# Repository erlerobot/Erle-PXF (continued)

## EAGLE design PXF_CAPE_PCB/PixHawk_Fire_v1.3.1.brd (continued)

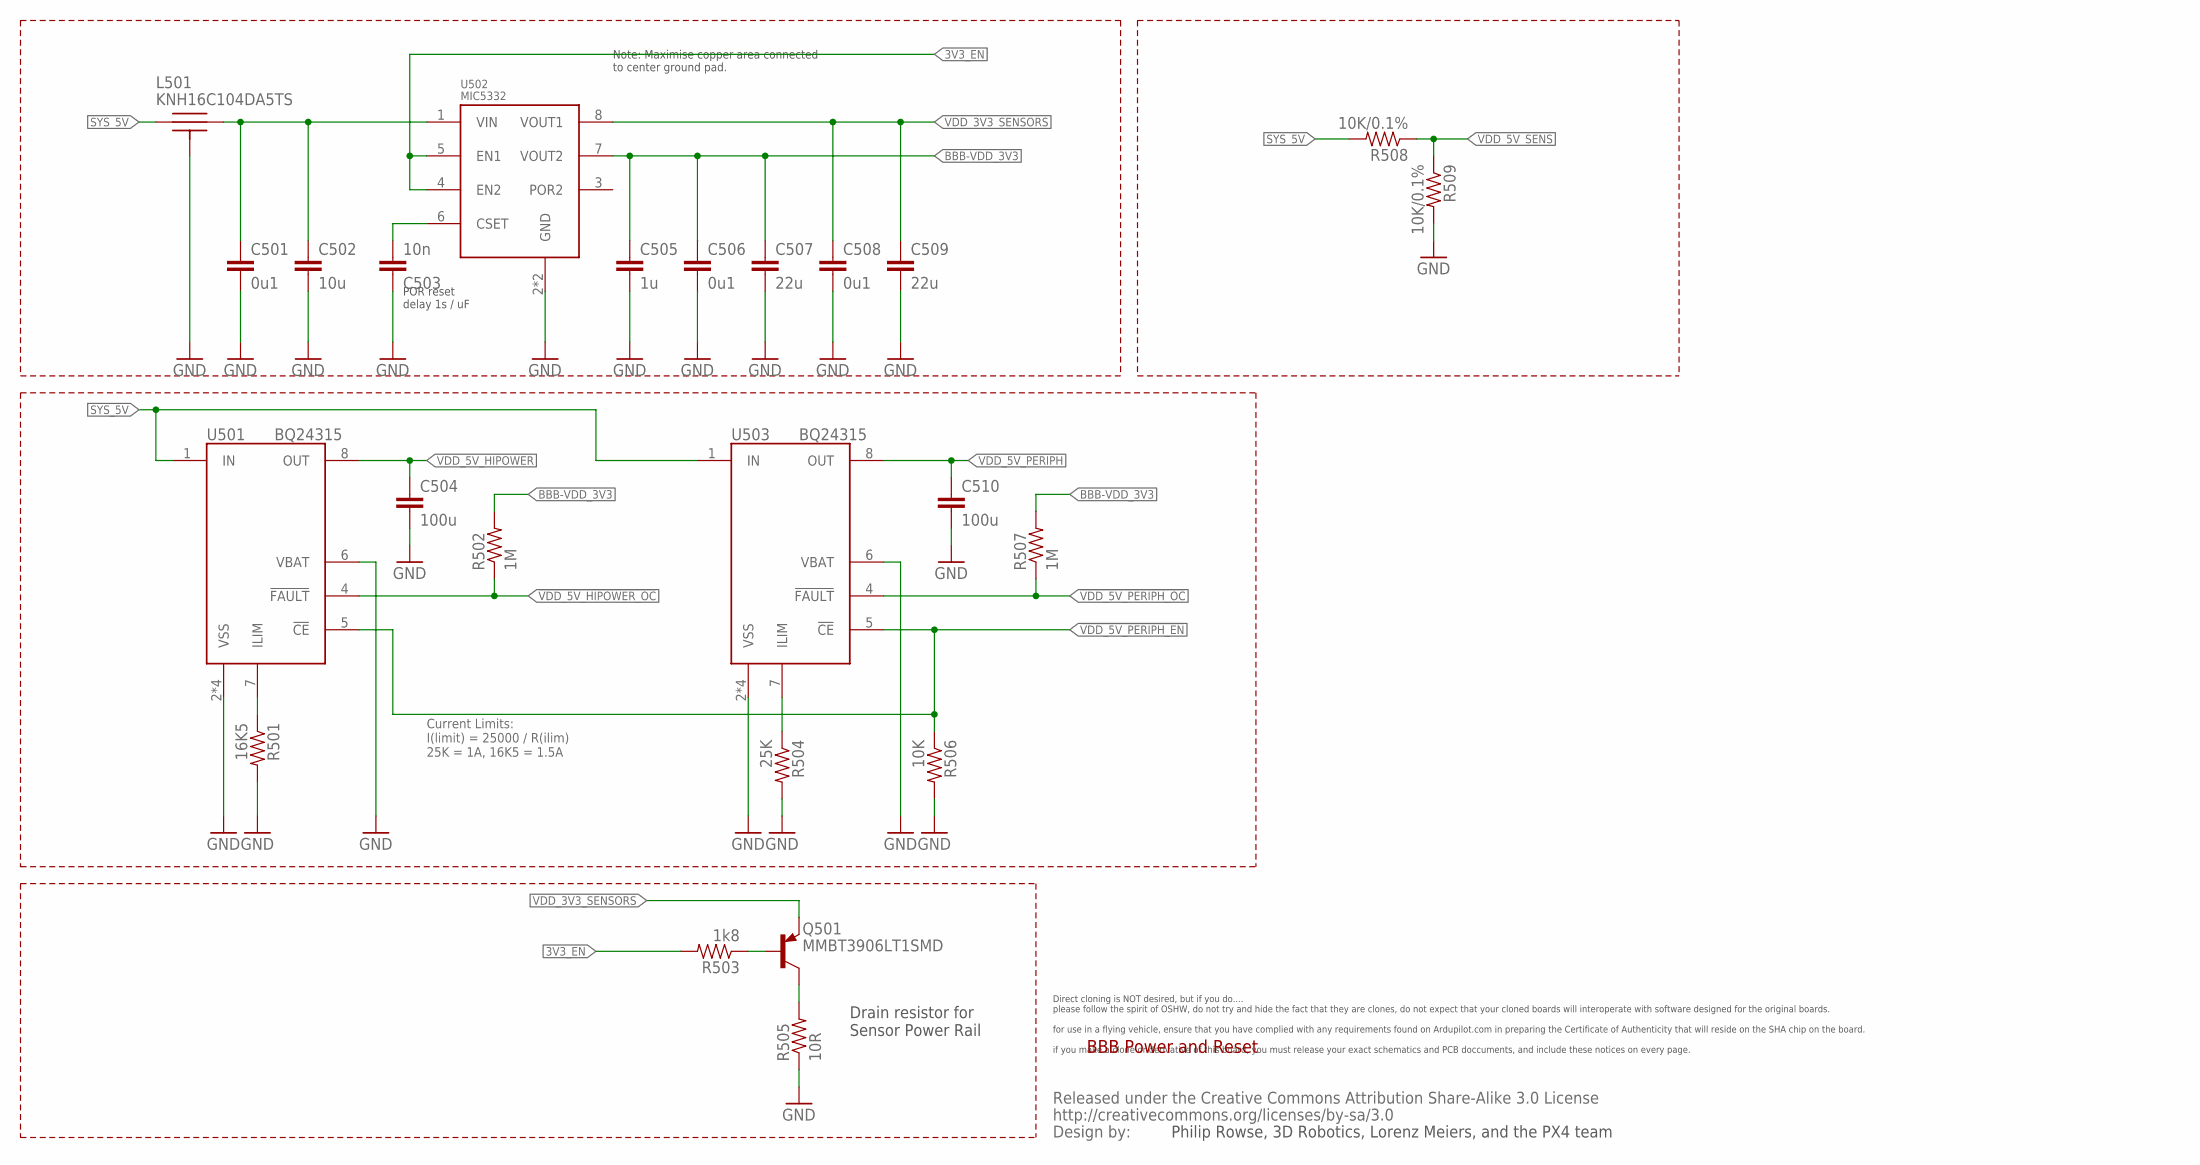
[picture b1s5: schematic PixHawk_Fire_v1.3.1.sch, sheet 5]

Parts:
C501, C506, C508: 0u1; 0402-CAP; PARTNO CC0402ZRY5V7BB104
C502: 10u; 0805-CAP; PARTNO C1608X7S0J106M080AC
C503: 10n; 0402-CAP; PARTNO CC0402KRX7R7BB103
C504, C510: 100u; 1206-CAP; PARTNO C3216X5R1A107M160AC
C505: 1u; 0603-CAP; PARTNO CC0603ZRY5V7BB105
C507, C509: 22u; 0805-CAP; PARTNO CC0805MKX5R5BB226
L501: KNH16C104DA5TS; KYOCERA-KNH16-DA; PARTNO KNH16C104DA5TS
Q501: MMBT3906LT1SMD; SOT23-BEC; PARTNO MMBT3906LT1G
R501: 16K5; 0402-RES; PARTNO RMCF0402FT16K5
R502, R507: 1M; 0402-RES; PARTNO MCR01MRTF1004
R503: 1k8; 0402-RES; PARTNO RC0402FR-071K8L
R504: 25K; 0402-RES; PARTNO RMCF0402FT25K5
R505: 10R; 0603-RES; PARTNO RC0402FR-0710RL
R506: 10K; 0402-RES; PARTNO ERA-2AEB103X
R508, R509: 10K/0.1%; 0402-RES; PARTNO ERA-2AEB103X
U501, U503: BQ24315; QFN8-DSG; PARTNO BQ24315DSGR
U502: MIC5332; MLF-8-EPAD; PARTNO MIC5332-SSYMT
U$9: CREATIVE_COMMONS

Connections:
3V3_EN: R503.P$2 (2), U502.4 (EN2), U502.5 (EN1); also elsewhere on the board
!VDD_5V_HIPOWER_OC: R502.P$1 (1), U501.4 (!FAULT); also elsewhere on the board
!VDD_5V_PERIPH_EN: R506.P$1 (1), U501.5 (!CE), U503.5 (!CE); also elsewhere on the board
!VDD_5V_PERIPH_OC: R507.P$1 (1), U503.4 (!FAULT); also elsewhere on the board
BBB-VDD_3V3: C505.P$1 (1), C506.P$1 (1), C507.P$1 (1), R502.P$2 (2), R507.P$2 (2), U502.7 (VOUT2); also elsewhere on the board
FMU-VDD_5V5: C501.P$1 (1), C502.P$1 (1), L501.P$2, U502.1 (VIN)
GND: C501.P$2 (2), C502.P$2 (2), C503.P$1 (1), C504.P$2 (2), C505.P$2 (2), C506.P$2 (2), C507.P$2 (2), C508.P$2 (2), C509.P$2 (2), C510.P$2 (2), L501.P$3, L501.P$4, L501.P$5, R501.P$2 (2), R504.P$2 (2), R505.1, R506.P$2 (2), R509.P$2 (2), U501.2 (VSS), U501.6 (VBAT), U501.GND (VSS), U501.P$2 (VSS), U501.P$3 (VSS), U502.2 (GND), U502.GND, U503.2 (VSS), U503.6 (VBAT), U503.GND (VSS), U503.P$2 (VSS), U503.P$3 (VSS); also elsewhere on the board
unnamed: C503.P$2 (2), U502.6 (CSET)
unnamed: R504.P$1 (1), U503.7 (ILIM)
unnamed: Q501.C, R505.2
unnamed: Q501.B, R503.P$1 (1)
unnamed: R501.P$1 (1), U501.7 (ILIM)
SYS_5V: L501.P$1, R508.P$2 (2), U501.1 (IN), U503.1 (IN); also elsewhere on the board
VDD_3V3_SENSORS: C508.P$1 (1), C509.P$1 (1), Q501.E, U502.8 (VOUT1); also elsewhere on the board
VDD_5V_HIPOWER: C504.P$1 (1), U501.8 (OUT); also elsewhere on the board
VDD_5V_PERIPH: C510.P$1 (1), U503.8 (OUT); also elsewhere on the board
VDD_5V_SENS: R508.P$1 (1), R509.P$1 (1); also elsewhere on the board

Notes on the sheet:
BBB Power and Reset
Note: Maximise copper area connected to center ground pad.
POR reset delay 1s / uF
Current Limits: I(limit) = 25000 / R(ilim) 25K = 1A, 16K5 = 1.5A
Drain resistor for Sensor Power Rail
Philip Rowse, 3D Robotics, Lorenz Meiers, and the PX4 team
Direct cloning is NOT desired, but if you do.... please follow the spirit of OSHW, do not try and hide the fact that they are clones, do not expect that your cloned boards will interoperate with software designed for the original boards. for use in a flying vehicle, ensure that you have complied wi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

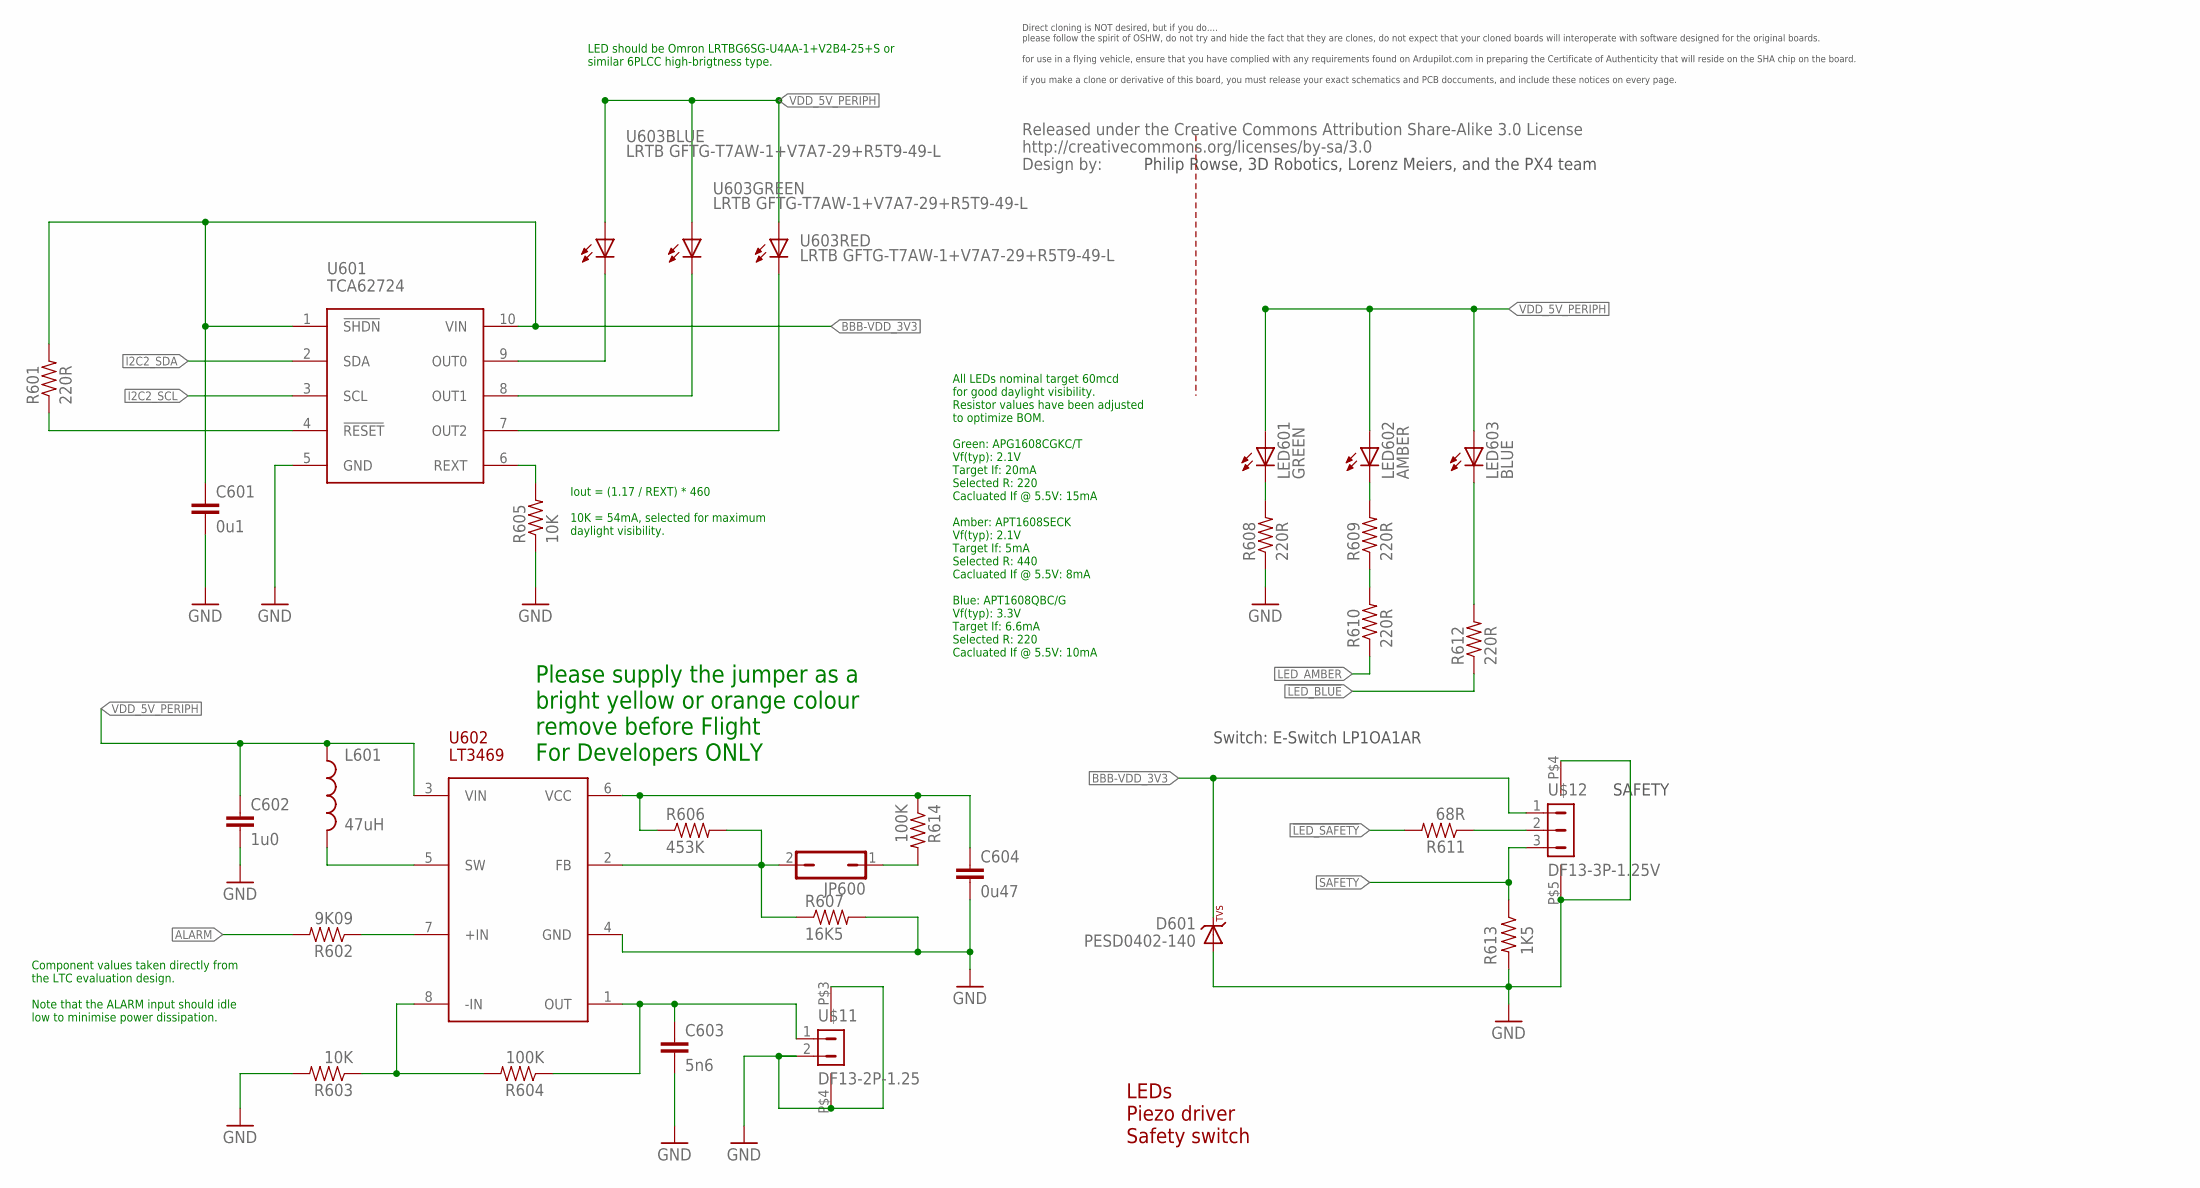
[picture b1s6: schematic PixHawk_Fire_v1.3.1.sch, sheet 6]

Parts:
C601: 0u1; 0402-CAP; PARTNO CC0402ZRY5V7BB104
C602: 1u0; 0603-CAP; PARTNO CC0603ZRY5V7BB105
C603: 5n6; 0402-CAP; PARTNO CC0402KRX7R7BB562
C604: 0u47; 0402-CAP; PARTNO C1005X5R1C474K050BC
D601: PESD0402-140; 0402-TVS; PARTNO PESD0402-140
JP600: JP1Q; JP1; PARTNO 1-87215-0
L601: 47uH; 0805-IND; PARTNO MLZ2012M470W
LED601: GREEN; 0603-LED; PARTNO APTD1608CGCK
LED602: AMBER; 0603-LED; PARTNO APTD1608SECK
LED603: BLUE; 0603-LED; PARTNO APTD1608QBC/D
R601, R608, R609, R610, R612: 220R; 0402-RES; PARTNO RC0402FR-07220RL
R602: 9K09; 0402-RES; PARTNO RMCF0402FT9K09
R603, R605: 10K; 0402-RES; PARTNO ERA-2AEB103X
R604, R614: 100K; 0402-RES; PARTNO RC0402FR-07100KL
R606: 453K; 0402-RES; PARTNO RMCF0402FT453K
R607: 16K5; 0402-RES; PARTNO RMCF0402FT16K5
R611: 68R; 0402-RES; PARTNO RC0402FR-0768RL
R613: 1K5; 0402-RES; PARTNO RC0402FR-071K5L
U601: TCA62724FMG; SON10; PARTNO TCA62724FMG
U602: LT3469; SOT23-8; PARTNO LT3469ETS8
U603: LRTB GFTG-T7AW-1+V7A7-29+R5T9-49-L; 6-PLCC; PARTNO LRTB GFTG-T7AW-1+V7A7-29+R5T9-49-L
U$10: CREATIVE_COMMONS
U$11: DF13-2P-1.25; DF13C-2P-1.25V; PARTNO DF13C-2P-1.25V(20)
U$12: DF13-3P-1.25V; DF13C-3P-1.25V; PARTNO DF13C-3P-1.25V(20)

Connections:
!LED_AMBER: R610.P$1 (1); also elsewhere on the board
!LED_BLUE: R612.P$1 (1); also elsewhere on the board
!LED_SAFETY: R611.P$2 (2); also elsewhere on the board
ALARM: R602.P$2 (2); also elsewhere on the board
BBB-VDD_3V3: C601.P$1 (1), D601.C, R601.P$2 (2), U601.1 (!SHDN), U601.10 (VIN), U$12.1; also elsewhere on the board
GND: C601.P$2 (2), C602.P$2 (2), C603.P$2 (2), C604.P$2 (2), D601.A, R603.P$2 (2), R605.P$1 (1), R607.P$2 (2), R608.P$1 (1), R613.P$2 (2), U601.5 (GND), U602.4 (GND), U$11.2, U$11.P$3, U$11.P$4, U$12.P$4, U$12.P$5; also elsewhere on the board
I2C2_SCL: U601.3 (SCL); also elsewhere on the board
I2C2_SDA: U601.2 (SDA); also elsewhere on the board
unnamed: R601.P$1 (1), U601.4 (!RESET)
unnamed: LED603.C, R612.P$2 (2)
unnamed: JP600.2, R606.P$2 (2), R607.P$1 (1), U602.2 (FB)
unnamed: R603.P$1 (1), R604.P$2 (2), U602.8 (-IN)
unnamed: C603.P$1 (1), R604.P$1 (1), U602.1 (OUT), U$11.1
unnamed: R602.P$1 (1), U602.7 (+IN)
unnamed: LED601.C, R608.P$2 (2)
unnamed: L601.P$2 (2), U602.5 (SW)
unnamed: C604.P$1 (1), R606.P$1 (1), R614.P$1 (1), U602.6 (VCC)
unnamed: R609.P$1 (1), R610.P$2 (2)
unnamed: LED602.C, R609.P$2 (2)
unnamed: JP600.1, R614.P$2 (2)
unnamed: R611.P$1 (1), U$12.2
unnamed: R605.P$2 (2), U601.6 (REXT)
RGB_LED_3: U601.9 (OUT0), U603.C1 (C)
RGB_LED_4: U601.8 (OUT1), U603.C2 (C)
RGB_LED_14: U601.7 (OUT2), U603.C3 (C)
SAFETY: R613.P$1 (1), U$12.3; also elsewhere on the board
VDD_5V_PERIPH: C602.P$1 (1), L601.P$1 (1), LED601.A, LED602.A, LED603.A, U602.3 (VIN), U603.A1 (A), U603.A2 (A), U603.A3 (A); also elsewhere on the board

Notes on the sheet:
LEDs Piezo driver Safety switch
Switch: E-Switch LP1OA1AR
SAFETY
LED should be Omron LRTBG6SG-U4AA-1+V2B4-25+S or similar 6PLCC high-brigtness type.
Iout = (1.17 / REXT) * 460 10K = 54mA, selected for maximum daylight visibility.
All LEDs nominal target 60mcd for good daylight visibility. Resistor values have been adjusted to optimize BOM. Green: APG1608CGKC/T Vf(typ): 2.1V Target If: 20mA Selected R: 220 Cacluated If @ 5.5V: 15mA Amber: APT1608SECK Vf(typ): 2.1V Target If: 5mA Selected R: 440 Cacluated If @ 5.5V: 8mA Blue: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
Component values taken directly from the LTC evaluation design. Note that the ALARM input should idle low to minimise power dissipation.
Please supply the jumper as a bright yellow or orange colour remove before Flight For Developers ONLY
Philip Rowse, 3D Robotics, Lorenz Meiers, and the PX4 team
Direct cloning is NOT desired, but if you do.... please follow the spirit of OSHW, do not try and hide the fact that they are clones, do not expect that your cloned boards will interoperate with software designed for the original boards. for use in a flying vehicle, ensure that you have complied wi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

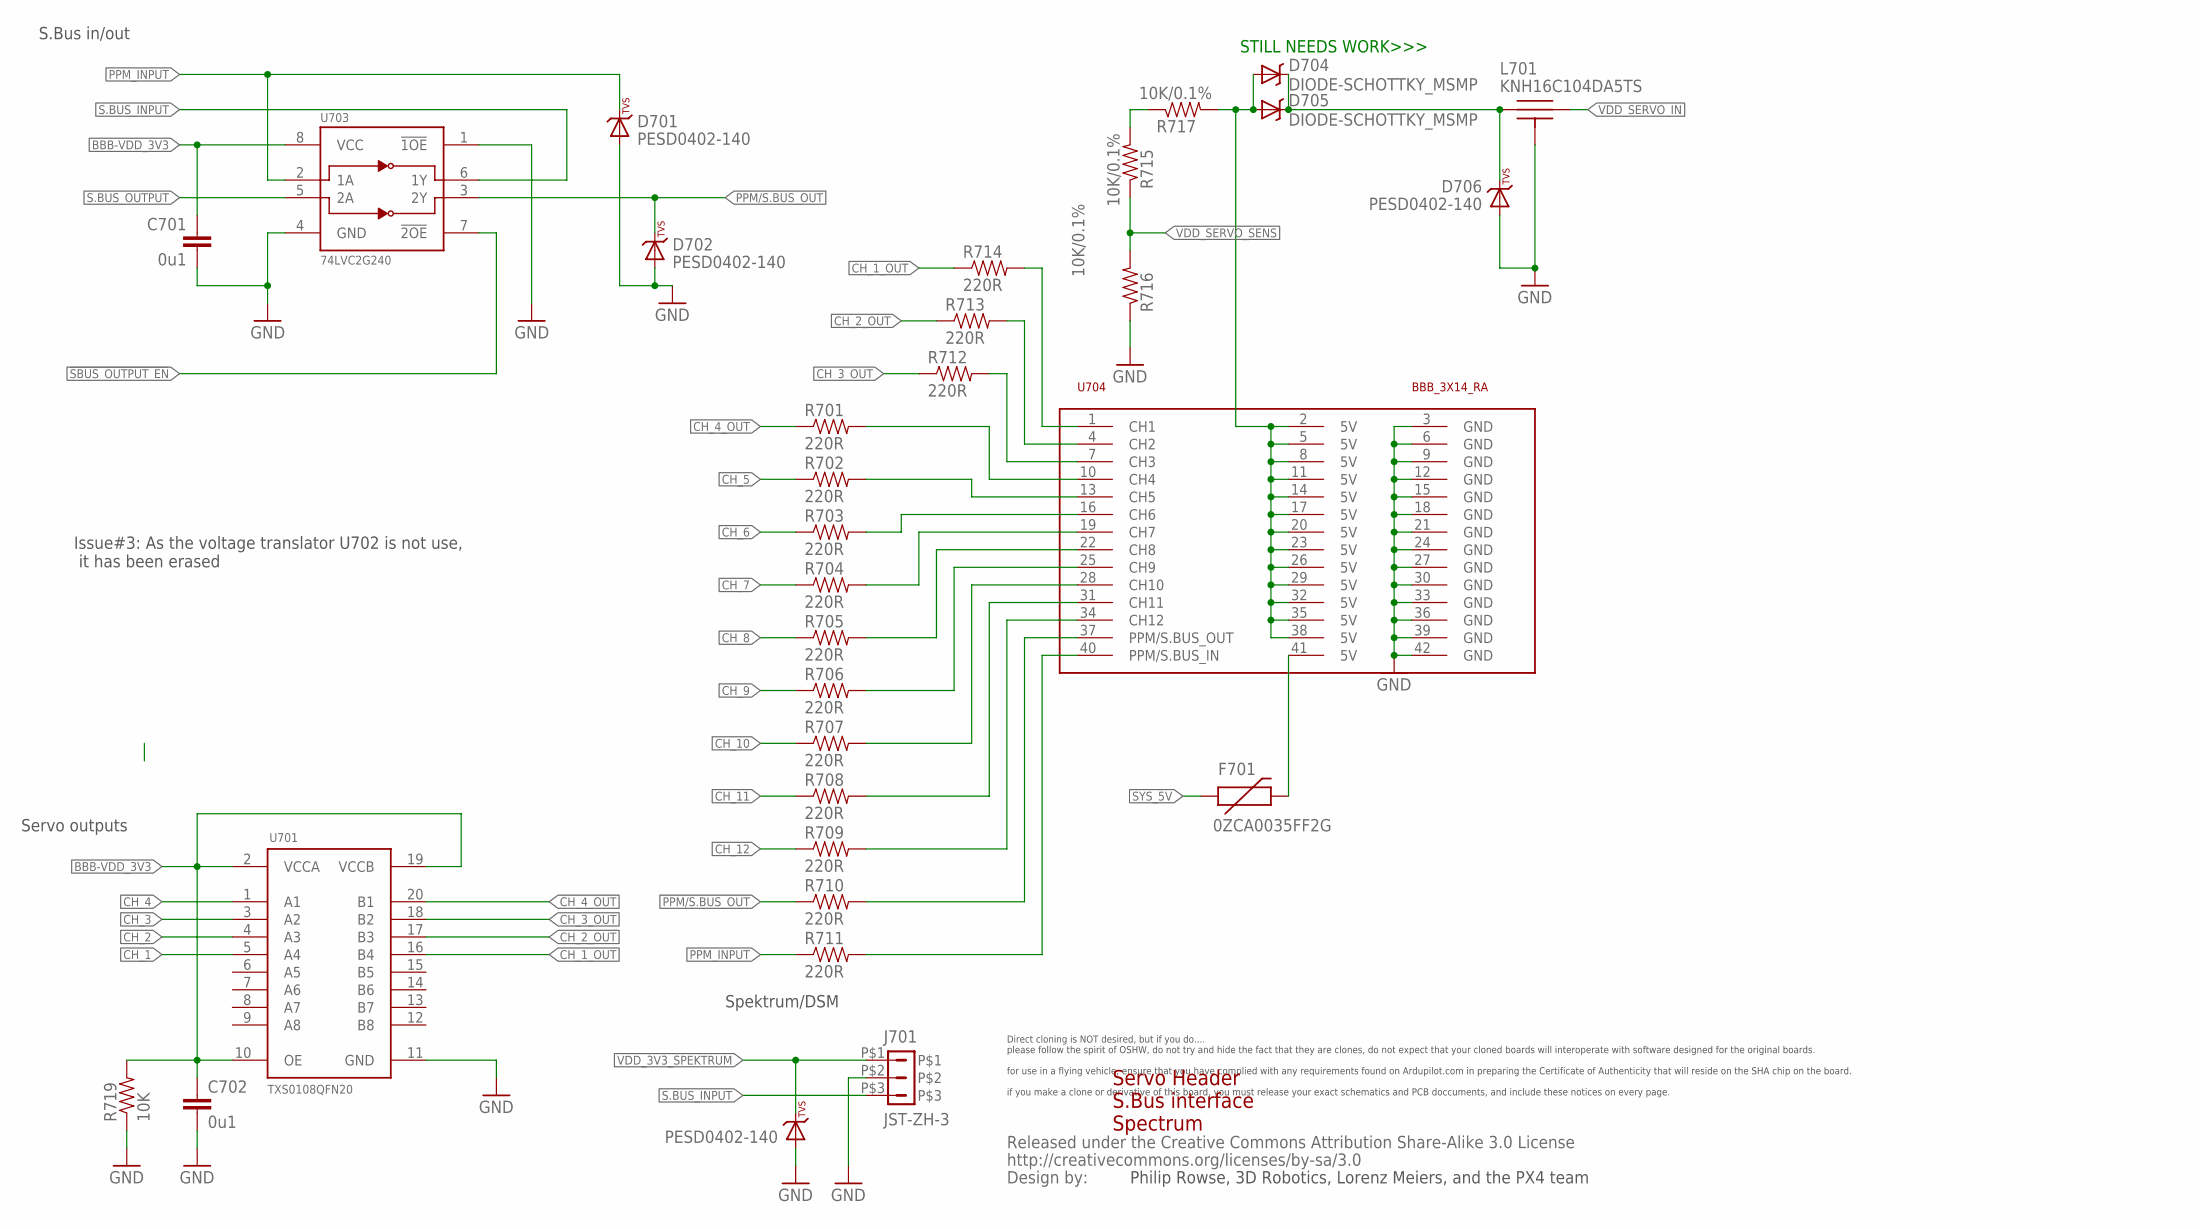
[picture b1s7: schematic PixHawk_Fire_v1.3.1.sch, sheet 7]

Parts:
C701, C702: 0u1; 0402-CAP; PARTNO CC0402ZRY5V7BB104
D701, D702, D703, D706: PESD0402-140; 0402-TVS; PARTNO PESD0402-140
D704, D705: DIODE-SCHOTTKY_MSMP; MICROSMP; PARTNO SS14
F701: 0ZCA0035FF2G; PTC-1206; PARTNO 0ZCA0035FF2G
J701: JST-ZH-3; JST-ZH-SMT-VERTICAL; PARTNO B3B-ZR-SM4-TF (LF)(SN)(P)
L701: KNH16C104DA5TS; KYOCERA-KNH16-DA; PARTNO KNH16C104DA5TS
R701, R702, R703, R704, R705, R706, R707, R708, R709, R710, R711, R712, R713, R714: 220R; 0402-RES; PARTNO RC0402FR-07220RL
R715, R716, R717: 10K/0.1%; 0402-RES; PARTNO ERA-2AEB103X
R719: 10K; 0402-RES; PARTNO ERA-2AEB103X
U701: TXS0108QFN20; QFN20-RGY; PARTNO TXS0108ERGYR
U703: 74LVC2G240; TSSOP8_SOT505-2; PARTNO 74LVC2G240DP,125
U704: BBB_3X14_RA; 3X14RA; PARTNO 07579
U$13: CREATIVE_COMMONS

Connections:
!SBUS_OUTPUT_EN: U703.7 (!2OE); also elsewhere on the board
BBB-VDD_3V3: C701.P$1 (1), C702.P$1 (1), R719.P$2 (2), U701.2 (VCCA), U701.10 (OE), U701.19 (VCCB), U703.8 (VCC); also elsewhere on the board
CH_1: U701.5 (A4); also elsewhere on the board
CH_1_OUT: R714.P$1 (1), U701.16 (B4)
CH_2: U701.4 (A3); also elsewhere on the board
CH_2_OUT: R713.P$1 (1), U701.17 (B3)
CH_3: U701.3 (A2); also elsewhere on the board
CH_3_OUT: R712.P$1 (1), U701.18 (B2)
CH_4: U701.1 (A1); also elsewhere on the board
CH_4_OUT: R701.P$1 (1), U701.20 (B1)
CH_5: R702.P$1 (1); also elsewhere on the board
CH_6: R703.P$1 (1); also elsewhere on the board
CH_7: R704.P$1 (1); also elsewhere on the board
CH_8: R705.P$1 (1); also elsewhere on the board
CH_9: R706.P$1 (1); also elsewhere on the board
CH_10: R707.P$1 (1); also elsewhere on the board
CH_11: R708.P$1 (1); also elsewhere on the board
CH_12: R709.P$1 (1); also elsewhere on the board
FMU-CH6-PROT: R708.P$2 (2), U704.31 (CH11)
GND: C701.P$2 (2), C702.P$2 (2), D701.A, D702.A, D703.A, D706.A, J701.P$2, L701.P$3, L701.P$4, L701.P$5, R716.P$1 (1), R719.P$1 (1), U701.11 (GND), U703.1 (!1OE), U703.4 (GND), U704.3 (GND), U704.6 (GND), U704.9 (GND), U704.12 (GND), U704.15 (GND), U704.18 (GND), U704.21 (GND), U704.24 (GND), U704.27 (GND), U704.30 (GND), U704.33 (GND), U704.36 (GND), U704.39 (GND), U704.42 (GND); also elsewhere on the board
IO-CH1-PROT: R707.P$2 (2), U704.28 (CH10)
IO-CH8-PROT: R712.P$2 (2), U704.7 (CH3)
unnamed: R715.P$2 (2), R717.P$1 (1)
unnamed: D704.CATHODE (C), D705.CATHODE (C), D706.C, L701.P$1
unnamed: D704.ANODE (A), D705.ANODE (A), R717.P$2 (2), U704.2 (5V), U704.5 (5V), U704.8 (5V), U704.11 (5V), U704.14 (5V), U704.17 (5V), U704.20 (5V), U704.23 (5V), U704.26 (5V), U704.29 (5V), U704.32 (5V), U704.35 (5V), U704.38 (5V)
unnamed: F701.2, U704.41 (5V)
unnamed: R701.P$2 (2), U704.10 (CH4)
unnamed: R709.P$2 (2), U704.34 (CH12)
unnamed: R702.P$2 (2), U704.13 (CH5)
unnamed: R703.P$2 (2), U704.16 (CH6)
unnamed: R704.P$2 (2), U704.19 (CH7)
unnamed: R705.P$2 (2), U704.22 (CH8)
unnamed: R706.P$2 (2), U704.25 (CH9)
unnamed: R710.P$2 (2), U704.37 (PPM/S.BUS_OUT)
unnamed: R711.P$2 (2), U704.40 (PPM/S.BUS_IN)
unnamed: R713.P$2 (2), U704.4 (CH2)
PPM-SBUS-PROT: R714.P$2 (2), U704.1 (CH1)
PPM/S.BUS_OUT: D702.C, R710.P$1 (1), U703.3 (2Y)
PPM_INPUT: D701.C, R711.P$1 (1), U703.2 (1A); also elsewhere on the board
S.BUS_INPUT: J701.P$3, U703.6 (1Y); also elsewhere on the board
S.BUS_OUTPUT: U703.5 (2A); also elsewhere on the board
SYS_5V: F701.1; also elsewhere on the board
VDD_3V3_SPEKTRUM: D703.C, J701.P$1; also elsewhere on the board
VDD_SERVO_IN: L701.P$2; also elsewhere on the board
VDD_SERVO_SENS: R715.P$1 (1), R716.P$2 (2); also elsewhere on the board

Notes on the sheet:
Servo Header S.Bus interface Spectrum
S.Bus in/out
Servo outputs
Spektrum/DSM
STILL NEEDS WORK>>>
Philip Rowse, 3D Robotics, Lorenz Meiers, and the PX4 team
Direct cloning is NOT desired, but if you do.... please follow the spirit of OSHW, do not try and hide the fact that they are clones, do not expect that your cloned boards will interoperate with software designed for the original boards. for use in a flying vehicle, ensure that you have complied wi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
Issue#3: As the voltage translator U702 is not use, it has been erased

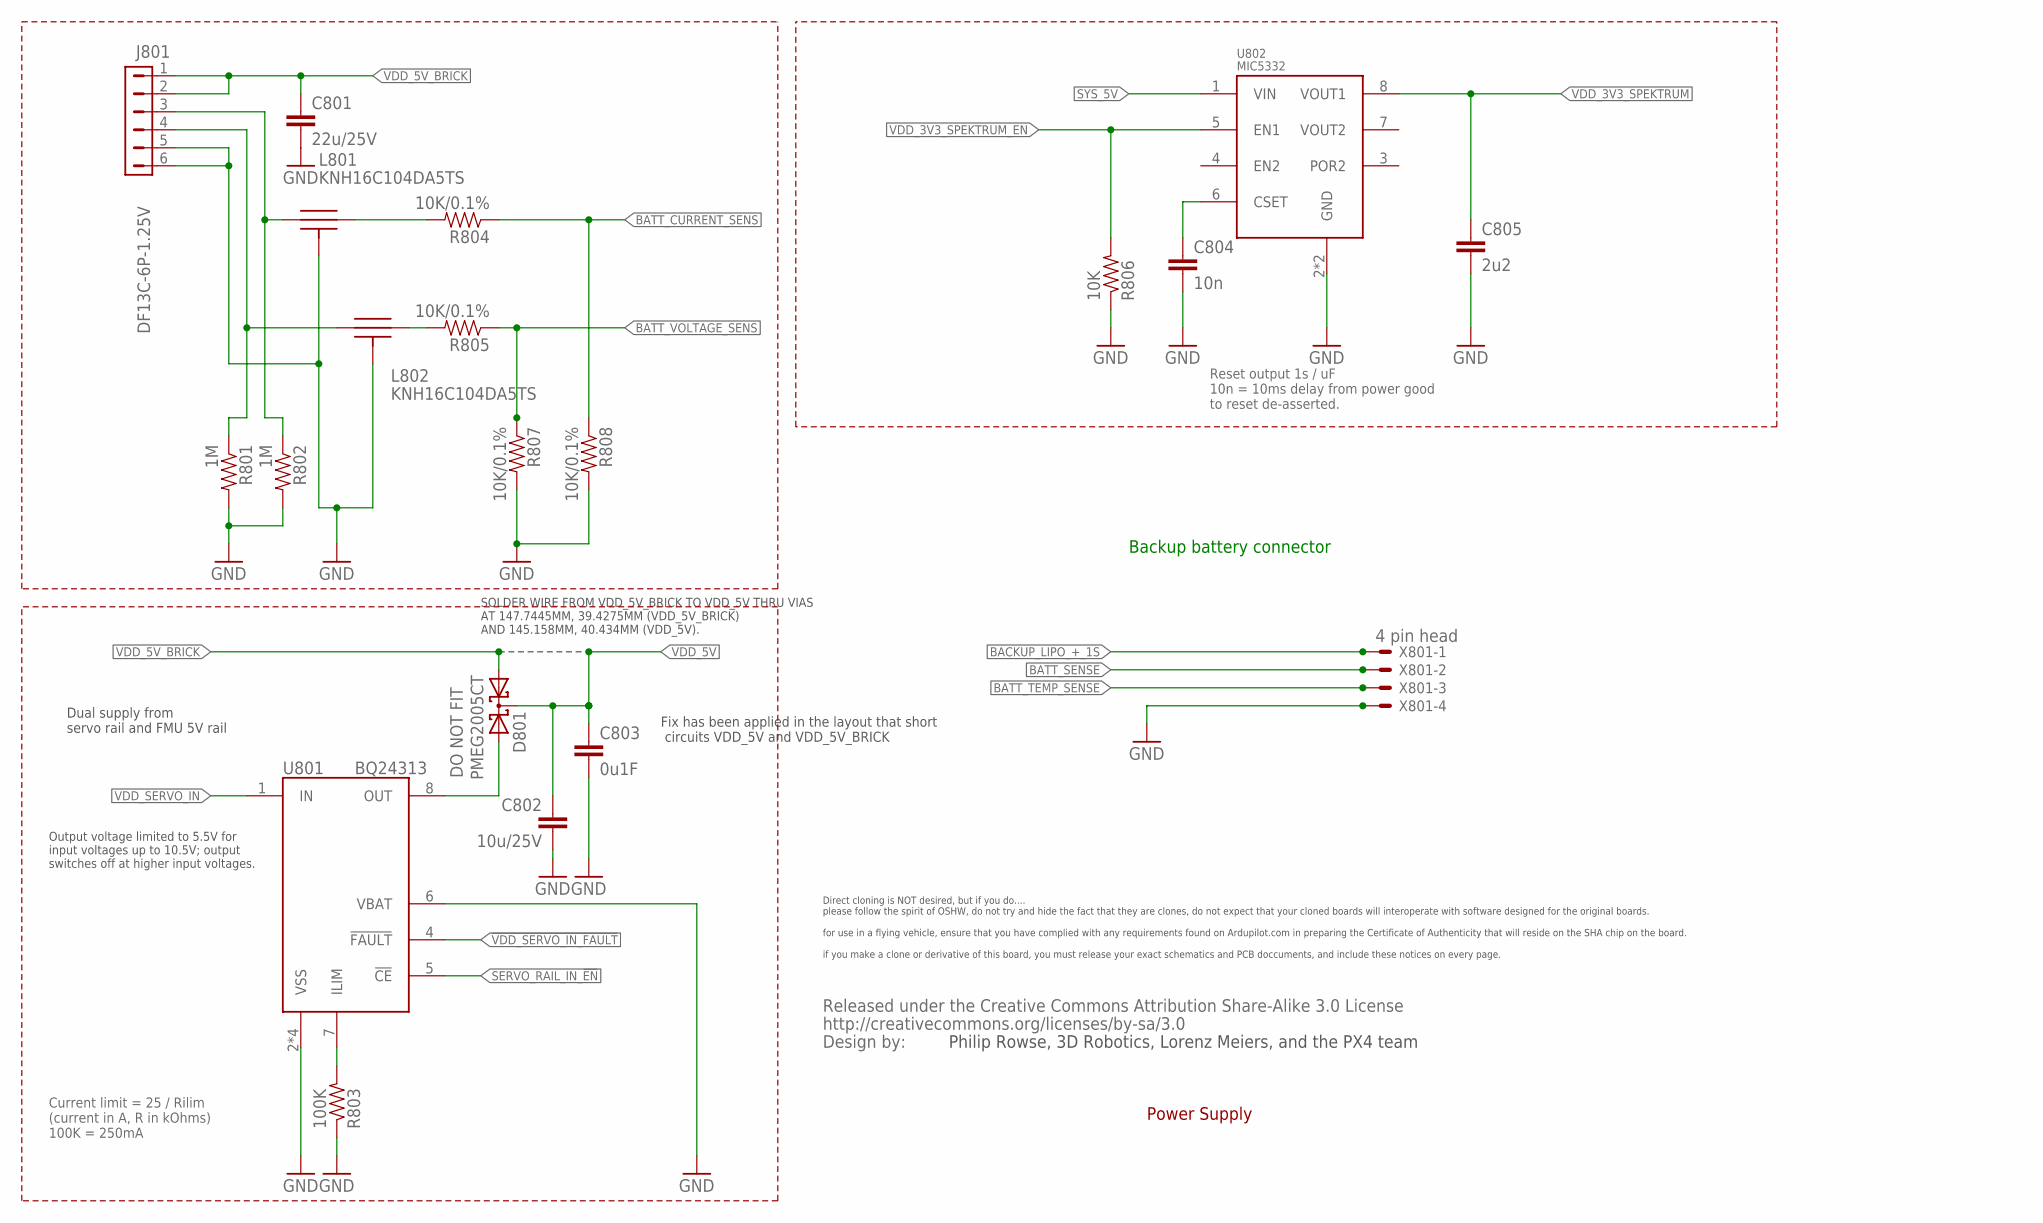
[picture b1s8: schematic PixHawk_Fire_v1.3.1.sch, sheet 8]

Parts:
C801: 22u/25V; 0805-CAP; PARTNO CL21A226MAQNNNE
C802: 10u/25V; 0805-CAP; PARTNO CL21A106KAYNNNE
C803: 0u1F; 0402-CAP; PARTNO CC0402ZRY5V7BB104
C804: 10n; 0402-CAP; PARTNO CC0402KRX7R7BB103
C805: 2u2; 0402-CAP; PARTNO CC0603ZRY5V6BB225
D801: PMEG2005CT; SOT23-3; PARTNO DO NOT FIT
J801: DF13C-6P-1.25V; PARTNO DF13C-6P-1.25V(20)
L801, L802: KNH16C104DA5TS; KYOCERA-KNH16-DA; PARTNO KNH16C104DA5TS
R801, R802: 1M; 0402-RES; PARTNO RC0402FR-071ML
R803: 100K; 0402-RES; PARTNO RC0402FR-07100KL
R804, R805, R807, R808: 10K/0.1%; 0402-RES; PARTNO ERA-2AEB103X
R806: 10K; 0402-RES; PARTNO ERA-2AEB103X
U801: BQ24313; QFN8-DSG; PARTNO BQ24313DSGT
U802: MIC5332; MLF-8-EPAD; PARTNO MIC5332-SSYMT
U$14: CREATIVE_COMMONS
X801: 4 pin head; 53047-04; PARTNO 53047-04

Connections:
!VDD_SERVO_IN_FAULT: U801.4 (!FAULT); also elsewhere on the board
BACKUP_LIPO_+_1S: X801.1; also elsewhere on the board
BATT_CURRENT_SENS: R804.P$1 (1), R808.P$1 (1); also elsewhere on the board
BATT_CURRENT_SENS_PROT: J801.3, L801.P$1, R802.P$1 (1)
BATT_SENSE: X801.2; also elsewhere on the board
BATT_TEMP_SENSE: X801.3; also elsewhere on the board
BATT_VOLTAGE_SENS: R805.P$1 (1), R807.P$1 (1); also elsewhere on the board
BATT_VOLTAGE_SENS_PROT: J801.4, L802.P$1, R801.P$1 (1)
GND: C801.P$2 (2), C802.P$2 (2), C803.P$2 (2), C804.P$2 (2), C805.P$2 (2), J801.5, J801.6, L801.P$3, L801.P$4, L801.P$5, L802.P$3, L802.P$4, L802.P$5, R801.P$2 (2), R802.P$2 (2), R803.P$1 (1), R806.P$1 (1), R807.P$2 (2), R808.P$2 (2), U801.2 (VSS), U801.6 (VBAT), U801.GND (VSS), U801.P$2 (VSS), U801.P$3 (VSS), U802.2 (GND), U802.GND, X801.4; also elsewhere on the board
unnamed: D801.2 (A2), U801.8 (OUT)
unnamed: R803.P$2 (2), U801.7 (ILIM)
unnamed: L802.P$2, R805.P$2 (2)
unnamed: L801.P$2, R804.P$2 (2)
unnamed: C804.P$1 (1), U802.6 (CSET)
SERVO_RAIL_IN_!EN: U801.5 (!CE); also elsewhere on the board
SYS_5V: U802.1 (VIN); also elsewhere on the board
VDD_3V3_SPEKTRUM: C805.P$1 (1), U802.8 (VOUT1); also elsewhere on the board
VDD_3V3_SPEKTRUM_EN: R806.P$2 (2), U802.5 (EN1); also elsewhere on the board
VDD_5V: C802.P$1 (1), C803.P$1 (1), D801.3 (CC); also elsewhere on the board
VDD_5V_BRICK: C801.P$1 (1), D801.1 (A1), J801.1, J801.2; also elsewhere on the board
VDD_SERVO_IN: U801.1 (IN); also elsewhere on the board

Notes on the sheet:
Dual supply from servo rail and FMU 5V rail
Current limit = 25 / Rilim (current in A, R in kOhms) 100K = 250mA
Power Supply
Reset output 1s / uF 10n = 10ms delay from power good to reset de-asserted.
Output voltage limited to 5.5V for input voltages up to 10.5V; output switches off at higher input voltages.
Backup battery connector
SOLDER WIRE FROM VDD_5V_BRICK TO VDD_5V THRU VIAS AT 147.7445MM, 39.4275MM (VDD_5V_BRICK) AND 145.158MM, 40.434MM (VDD_5V).
Philip Rowse, 3D Robotics, Lorenz Meiers, and the PX4 team
Direct cloning is NOT desired, but if you do.... please follow the spirit of OSHW, do not try and hide the fact that they are clones, do not expect that your cloned boards will interoperate with software designed for the original boards. for use in a flying vehicle, ensure that you have complied wi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
Fix has been applied in the layout that short circuits VDD_5V and VDD_5V_BRICK

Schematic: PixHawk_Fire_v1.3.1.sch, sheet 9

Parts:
ADC_PR: PAD.04; PAD.04X.04; PARTNO *
CAN_H: PAD.04; PAD.04X.04; PARTNO *
CAN_L: PAD.04; PAD.04X.04; PARTNO *
GND, GND.: PAD.04; PAD.04X.04; PARTNO *
JP901, JP902: FIDUCIAL1.5X3; FIDUCIAL-1.5X3; PARTNO *
M3_MOUNT901, M3_MOUNT902, M3_MOUNT903, M3_MOUNT904: MOUNT-HOLE3.1MM; MOUNT-HOLE3.1; PARTNO *
OSHW_LOGO: OSHW-LOGOS; OSHW-LOGO-S; PARTNO *
S1RX, S1TX, S2RX, S2TX, S3RX, S3TX, S4RX, S4TX: PAD.04; PAD.04X.04; PARTNO *
U$15: CREATIVE_COMMONS
VDDA_3V901: PAD.04; PAD.04X.04; PARTNO *
VDD_3V901, VDD_5V_BRICK, VDD_5V_IN: PAD.04; PAD.04X.04; PARTNO *

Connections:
BBB-VDD_3V3: VDD_3V901.P$1; also elsewhere on the board
CAN_H: CAN_H.P$1; also elsewhere on the board
CAN_L: CAN_L.P$1; also elsewhere on the board
GND: GND.P$1, GND..P$1; also elsewhere on the board
PRESSURE_SENS_IN: ADC_PR.P$1; also elsewhere on the board
S.BUS_INPUT: S3RX.P$1; also elsewhere on the board
S.BUS_OUTPUT: S3TX.P$1; also elsewhere on the board
SERIAL1_RX: S1RX.P$1; also elsewhere on the board
SERIAL1_TX: S1TX.P$1; also elsewhere on the board
SERIAL2_RX: S2RX.P$1; also elsewhere on the board
SERIAL2_TX: S2TX.P$1; also elsewhere on the board
SERIAL4_RX: S4RX.P$1; also elsewhere on the board
SERIAL4_TX: S4TX.P$1; also elsewhere on the board
SYS_5V: VDD_5V_IN.P$1; also elsewhere on the board
VDD_3V3_SENSORS: VDDA_3V901.P$1; also elsewhere on the board
VDD_5V_BRICK: VDD_5V_BRICK.P$1; also elsewhere on the board

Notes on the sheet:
Mounting holes to suit M3 fastener
and Richco R908 series spacer.
Use R908-5 spacers to stack with
other PX4 series boards (7.95 mm).
Production Testing Pads
Test and Fiducials
Minimum drill: 0.3 mm
Minimum trace width (use mm for traces): 0.15 mm
Minimum copper distance (all signals): 0.15 mm
Dimension / hole minimum distance: 0.2 mm
Layout grid: 4 mil, part grid: 4 mil. Dimensions / hole positions: 0.5 mm
Board: FR4 black, 1.0 mm. Solder stop on vias < 0.6 mm.
Signoff rules: Footprint checked, pinmap checked, schematic checked, cross-references to other pages checked.
Routing: 1: general/escape 2: ground 3: horizontal 4: vertical 5: power 6: general/escape
Fiducials for machine vision alignment.
Parts: Resistors: 0402 / 1% unless specified otherwise Capacitors: 0402 to 1206, ceramic, voltage rating: 10V unless specified
Philip Rowse, 3D Robotics, Lorenz Meiers, and the PX4 team
Direct cloning is NOT desired, but if you do.... please follow the spirit of OSHW, do not try and hide the fact that they are clones, do not expect that your cloned boards will interoperate with software designed for the original boards. for use in a flying vehicle, ensure that you have complied wi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

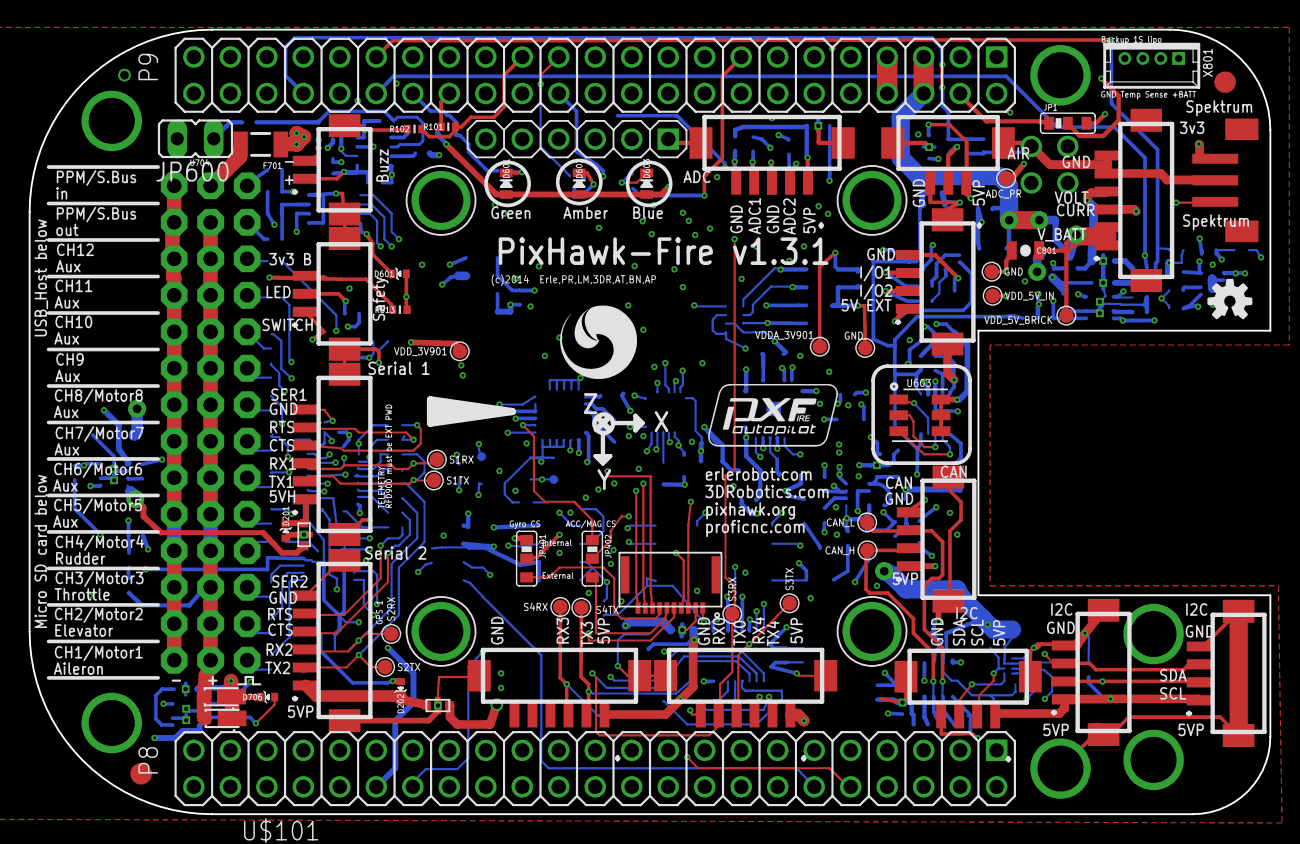
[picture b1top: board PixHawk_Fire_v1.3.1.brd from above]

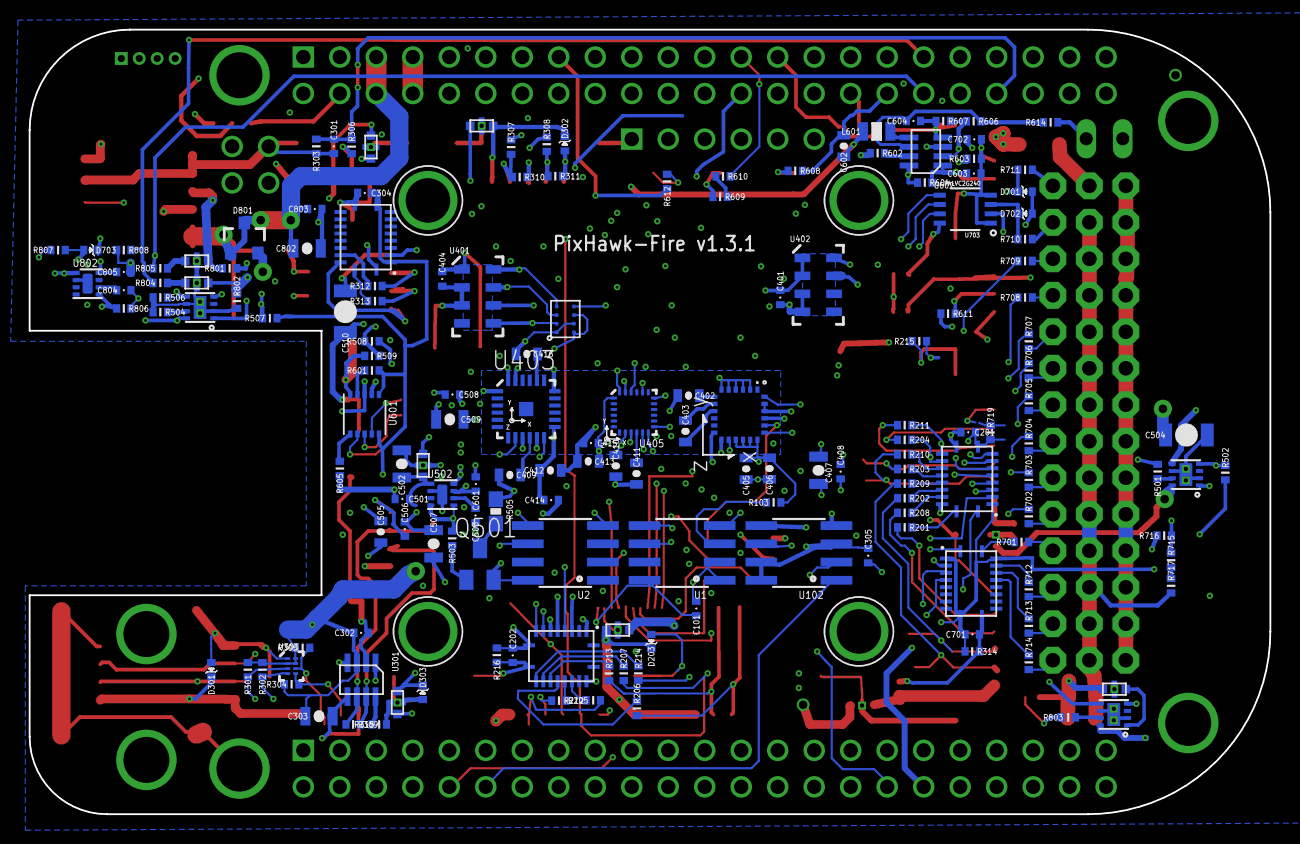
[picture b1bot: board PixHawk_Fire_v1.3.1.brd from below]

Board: 6 copper layers, 86.4 x 54.6 mm, 239 parts (165 on the bottom side), 191 nets.

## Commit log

2014-08-11 v1.1 with errors
2014-08-13 Creation of v1.2, LSM9DSO issue fixed
    Sch and brd v1.2 creation and LSM9DSO issue reparation according to
    feedback
2014-08-26 Fix into gitignore
2014-08-26 Fix in the layout names
2014-09-01 Fixes in some typos with components
2014-09-11 ISSUE#3 Fix
    Bypassing of the voltage translator. Modified pins: P8:
    33,35,39,40,41,42,43,44,45,46. Which are the signlas : USART4 RTS abd
    CTS nad CH6 to CH12
2014-09-17 ISSUE#3 v2: Removal of the Voltage Trns. U702
    Removal of U702, R718 and C703. Retracing of this area. Notice there is
    a airwire in point 3880,929.5. I have tried to remove it with little
    success.
2014-09-23 Address issue #2.
    This fix avoid having to hand solder a cable
    between VDD_5V and VDD_5V_BRICK. The fix
    allows to use the Power Module to power the
    board directly.
2014-09-23 Minor fixes in the silscreen
2014-09-30 Remove manufaturing files from git
2014-10-01 MPU6500 instead of MPU9250
    MPU9250 replacement for MPU6500. Minimal changes have been done: C411
    and C415 value change to .1uF. Model change of both Cs in order to
    fulfill X7R and 10% type requeriments.
2014-10-02 Version 1.4, LSM9D -> MPU9255 change
2014-10-02 Capacitor value and partno fix
2014-10-03 MPU9255 testpad addition
    MPU9255 testpad addition, so is possible to solder a wire to make the
    next connection: MPU pin 1 ->3v3
    U404 /CS conexion fix
2014-10-07 PXF v1.3.1: Issue #11 fix
    Fix of the Issue #11:
    - LSM9D: pin -> NC and Pin 15, 16,17- > pin 18 connection
    - MPU9250 : Pin 1 -> 3v3
2014-10-08 Modify README, minor changes in the board layout
